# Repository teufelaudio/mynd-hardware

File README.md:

# Teufel MYND Hardware Repository
This repository contains all hardware related files including 3d models, schematics and pcb-layout files in various formats.

# Project structure
## `CAD/`
Contains 3d construction files in Rhino, STEP and STL formats. 
For every format, individual parts are available as direct download or a 'complete' package is avialable containing the entire model.
Due to size, the complete model in STL format is compressed into 'complete.zip'.

## `PCB_Schematics/`
### `./Altium`
Contains Altium Designer PCB and schematic files for all PCBs.
### `./KiCad`
Contains KiCad PCB and schematic files for all PCBs. Please note: These files were converted from the Altium working files for convenience and may still contain some  conversion errors.
### `./PDF`
Contains all schematic and assembly drawings exported to PDF from Altium files.

## Don't Yet Own a MYND Speaker!?
Purchase one [here](https://teufel.de/mynd)!

# Clone
```shell
git clone git@github.com:teufelaudio/mynd-hardware.git
```

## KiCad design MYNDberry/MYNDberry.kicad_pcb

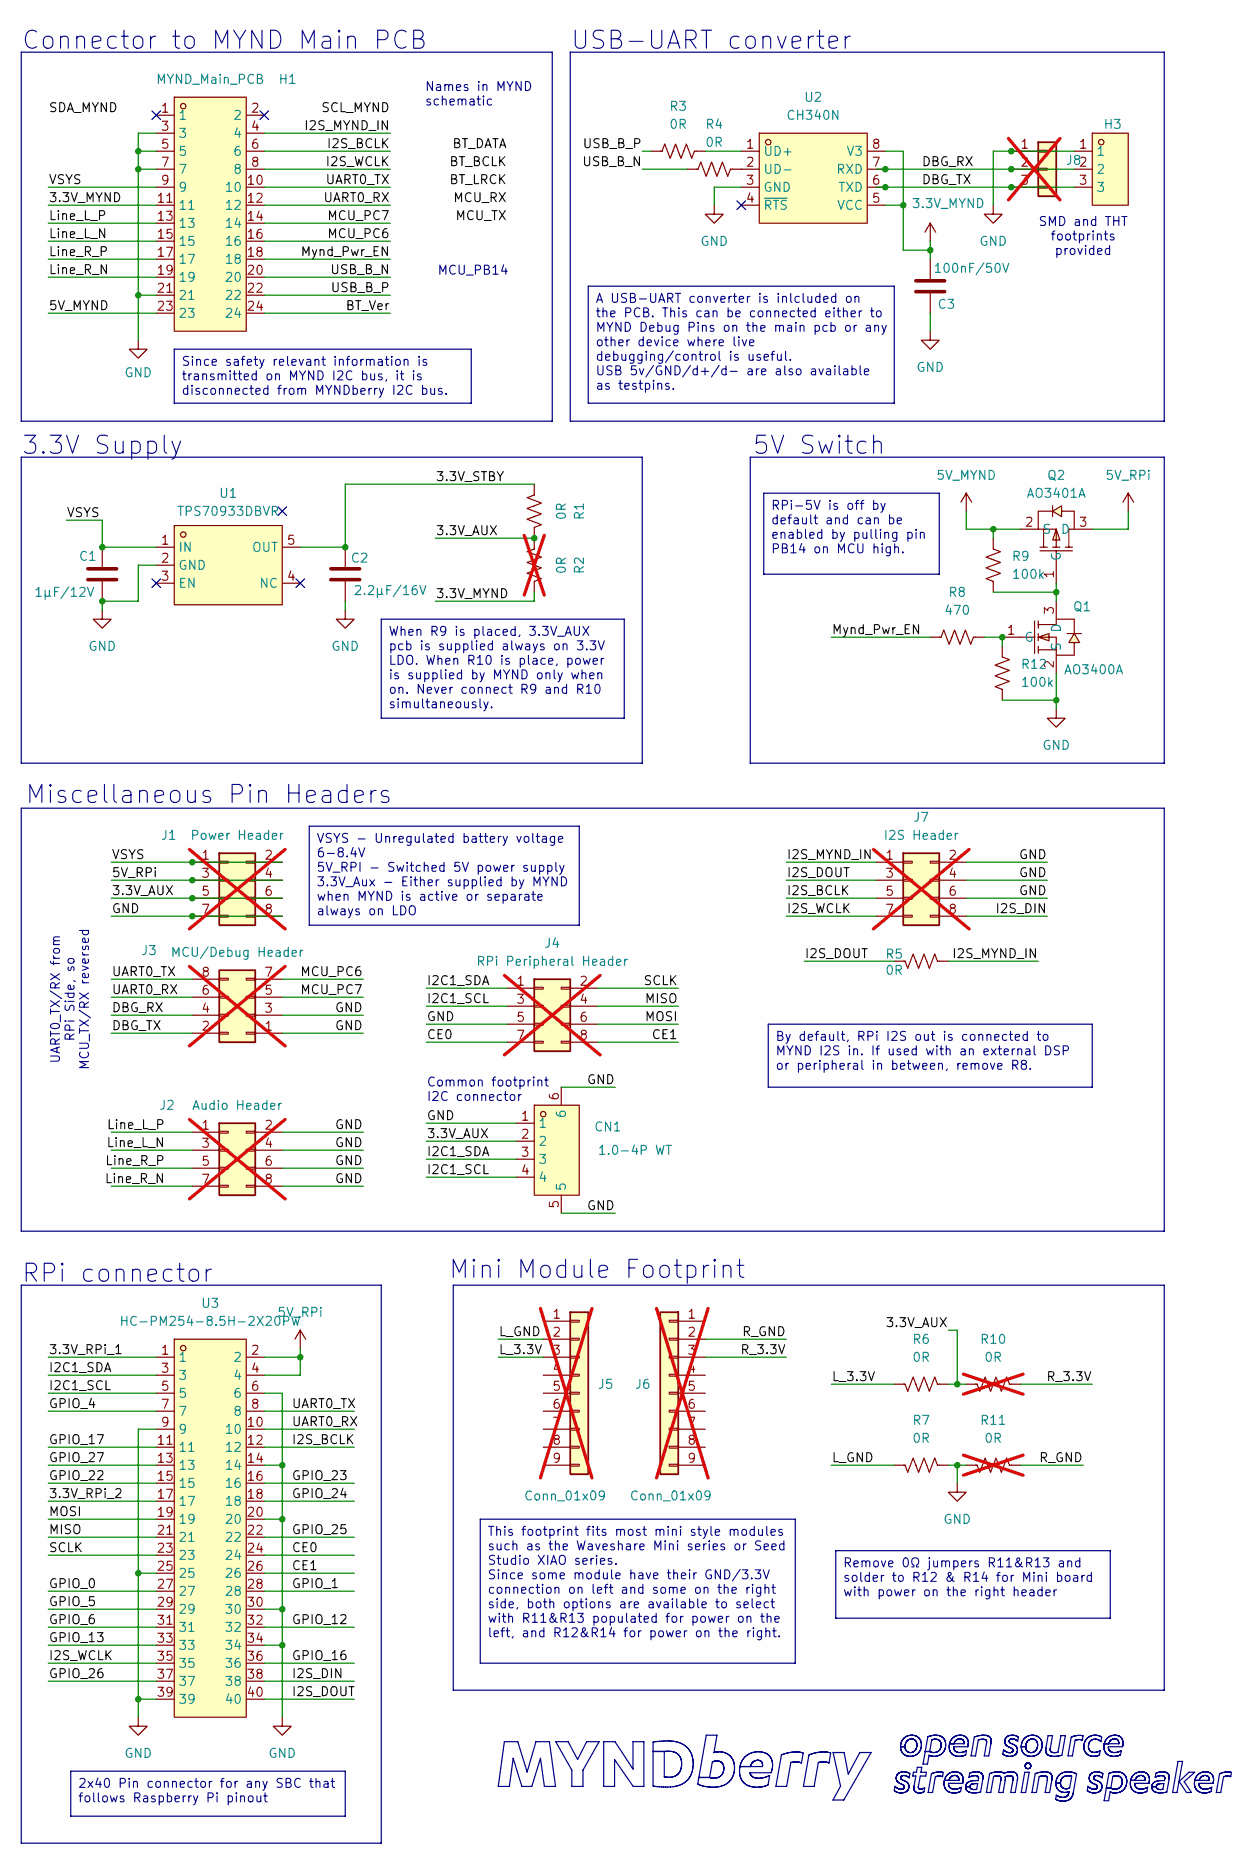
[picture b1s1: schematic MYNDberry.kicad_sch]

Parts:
C1: 1µF/12V; C_0603_1608Metric; LCSC C15008
C2: 2.2µF/16V; C_0603_1608Metric; LCSC C15008
C3: 100nF/50V; C_0603_1608Metric; LCSC C15008
CN1: 1.0-4P WT; CONN-SMD_4P-P1.00_SHOU-HAN_1.0-4P-WT; LCSC Part C2906270
H1: MYND_Main_PCB; HDR-SMD_24P-P2.54-V-F-R2-C12-S7.4; LCSC Part C3294470
H3: HX_PZ2.54-1X3P_WT; HDR-SMD_3P-P2.54-H-M_KH-2.54PH-1X3P-L13.5-WT; LCSC Part C46061676
J1: Power Header; PinHeader_2x04_P2.54mm_Small_Outline; not fitted
J2: Audio Header; PinHeader_2x04_P2.54mm_Small_Outline; not fitted
J3: MCU/Debug Header; PinHeader_2x04_P2.54mm_Small_Outline; not fitted
J4: RPi Peripheral Header; PinHeader_2x04_P2.54mm_Small_Outline; not fitted
J5: Conn_01x09; 9P_SolderPad_TH_Left; not fitted
J6: Conn_01x09; 9P_SolderPad_TH_Right; not fitted
J7: I2S Header; PinHeader_2x04_P2.54mm_Small_Outline; not fitted
J8: Conn_01x03; PinHeader_1x03_P2.54mm_Vertical; not fitted
Q1: AO3400A; SOT-23-3_L2.9-W1.3-P1.90-LS2.4-BR; LCSC Part C20917
Q2: AO3401A; SOT-23_L2.9-W1.3-P1.90-LS2.4-BR; LCSC Part C15127
R1, R3, R4, R5, R6, R7: 0R; R_0603_1608Metric; LCSC Part C21189
R2, R10, R11: 0R; R_0603_1608Metric; not fitted
R8: 470; R_0603_1608Metric; LCSC Part C23179
R9, R12: 100k; R_0603_1608Metric; LCSC Part C25803
U1: TPS70933DBVR; SOT-23-5_L3.0-W1.7-P0.95-LS2.8-BR; LCSC Part C89347
U2: CH340N; SOP-8_L4.9-W3.9-P1.27-LS6.0-BL; LCSC Part C2977777
U3: HC-PM254-8.5H-2X20PW; HDR-TH_40P-P2.54-H-F-R2-C20-S2.54-N; LCSC Part C22373943

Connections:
3.3V_MYND: C3.2, H1.11, R2.2, U2.5 (VCC), U2.8 (V3)
5V_MYND: H1.23, Q2.2 (S), R9.2
5V_RPi: J1.3, J1.4, Q2.3 (D), U3.2, U3.4
/3.3V_AUX: CN1.2, J1.5, J1.6, R1.2, R2.1, R6.2, R10.1
/3.3V_RPi_1: U3.1
/3.3V_RPi_2: U3.17
/3.3V_STBY: C2.2, R1.1, U1.5 (OUT)
/BT_Ver: H1.24
/CE0: J4.7, U3.24
/CE1: J4.8, U3.26
/DBG_RX: H3.2, J3.4, J8.2, U2.7 (RXD)
/DBG_TX: H3.3, J3.2, J8.3, U2.6 (TXD)
/GPIO_0: U3.27
/GPIO_1: U3.28
/GPIO_4: U3.7
/GPIO_5: U3.29
/GPIO_6: U3.31
/GPIO_12: U3.32
/GPIO_13: U3.33
/GPIO_16: U3.36
/GPIO_17: U3.11
/GPIO_22: U3.15
/GPIO_23: U3.16
/GPIO_24: U3.18
/GPIO_25: U3.22
/GPIO_26: U3.37
/GPIO_27: U3.13
/I2C1_SCL: CN1.4, J4.3, U3.5
/I2C1_SDA: CN1.3, J4.1, U3.3
/I2S_BCLK: H1.6, J7.5, U3.12
/I2S_DIN: J7.8, U3.38
/I2S_DOUT: J7.3, R5.1, U3.40
/I2S_MYND_IN: H1.4, J7.1, R5.2
/I2S_WCLK: H1.8, J7.7, U3.35
/L_3.3V: J5.3, R6.1
/L_GND: J5.2, R7.1
/Line_L_N: H1.15, J2.3
/Line_L_P: H1.13, J2.1
/Line_R_N: H1.19, J2.7
/Line_R_P: H1.17, J2.5
/MCU_PC6: H1.16, J3.7
/MCU_PC7: H1.14, J3.5
/MISO: J4.4, U3.21
/MOSI: J4.6, U3.19
/Mynd_Pwr_EN: H1.18, R8.2
/R_3.3V: J6.3, R10.2
/R_GND: J6.2, R11.2
/SCLK: J4.2, U3.23
/UART0_RX: H1.12, J3.6, U3.10
/UART0_TX: H1.10, J3.8, U3.8
/USB_B_N: H1.20, R4.2
/USB_B_P: H1.22, R3.2
/VSYS: C1.2, H1.9, J1.1, J1.2, U1.1 (IN)
GND: C1.1, C2.1, C3.1, CN1.1, CN1.5, CN1.6, H1.3, H1.5, H1.7, H1.21, H3.1, J1.7, J1.8, J2.2, J2.4, J2.6, J2.8, J3.1, J3.3, J4.5, J7.2, J7.4, J7.6, J8.1, Q1.2 (S), R7.2, R11.1, R12.1, U1.2 (GND), U2.3 (GND), U3.6, U3.9, U3.14, U3.20, U3.25, U3.30, U3.34, U3.39
unnamed: Q1.3 (D), Q2.1 (G), R9.1
unnamed: Q1.1 (G), R8.1, R12.2
unnamed: R3.1, U2.1 (UD+)
unnamed: R4.1, U2.2 (UD-)

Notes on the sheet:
RPi connector
SMD and THT footprints provided
Miscellaneous Pin Headers
3.3V Supply
Mini Module Footprint
USB-UART converter
Connector to MYND Main PCB
MCU_PB14
5V Switch
UART0_TX/RX from RPi Side, so MCU_TX/RX reversed
Common footprint I2C connector
Names in MYND schematic
When R9 is placed, 3.3V_AUX pcb is supplied always on 3.3V LDO. When R10 is place, power is supplied by MYND only when on. Never connect R9 and R10 simultaneously.
This footprint fits most mini style modules such as the Waveshare Mini series or Seed Studio XIAO series. Since some module have their GND/3.3V connection on left and some on the right side, both options are available to select with R11&R13 populated for power on the left, and R12&R14 for power on 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
Since safety relevant information is transmitted on MYND I2C bus, it is disconnected from MYNDberry I2C bus.
Remove 0Ω jumpers R11&R13 and solder to R12 & R14 for Mini board with power on the right header
By default, RPi I2S out is connected to MYND I2S in. If used with an external DSP or peripheral in between, remove R8.
VSYS - Unregulated battery voltage 6-8.4V 5V_RPI - Switched 5V power supply 3.3V_Aux - Either supplied by MYND when MYND is active or separate always on LDO
A USB-UART converter is inlcluded on the PCB. This can be connected either to MYND Debug Pins on the main pcb or any other device where live debugging/control is useful. USB 5v/GND/d+/d- are also available as testpins.
RPi-5V is off by default and can be enabled by pulling pin PB14 on MCU high.
2x40 Pin connector for any SBC that follows Raspberry Pi pinout

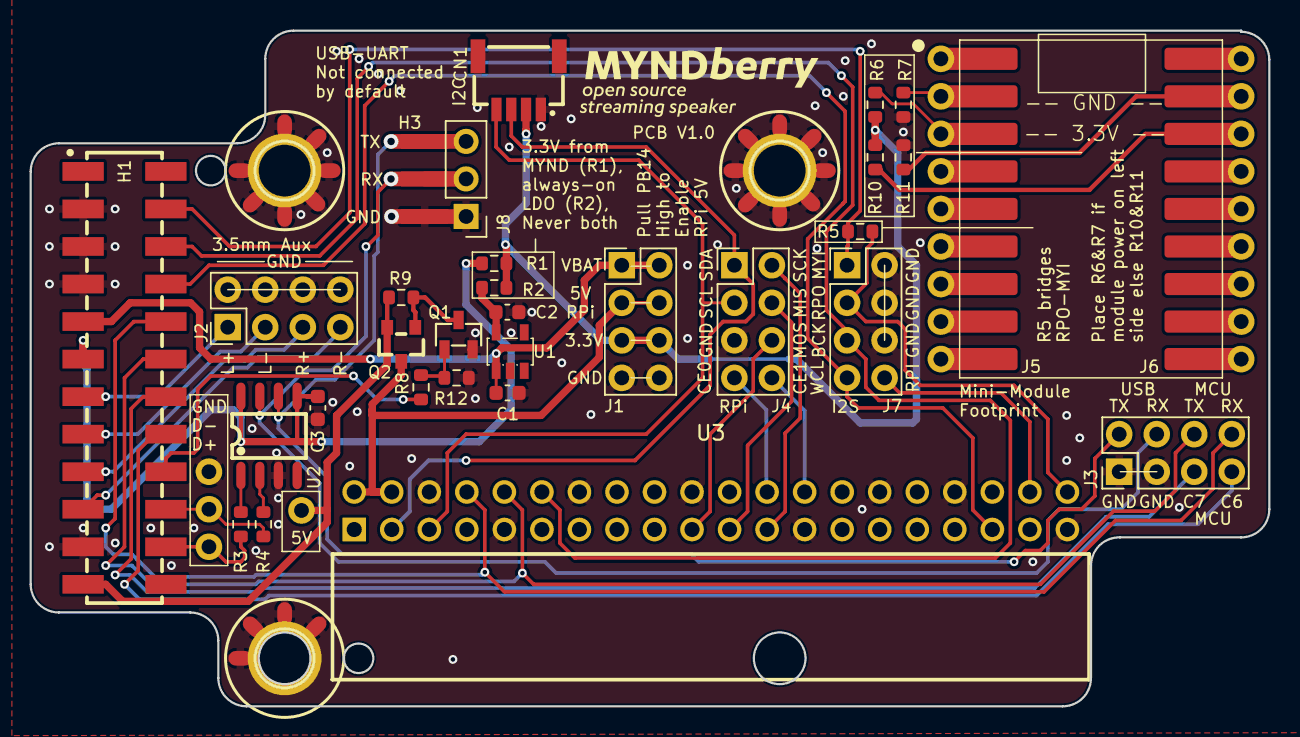
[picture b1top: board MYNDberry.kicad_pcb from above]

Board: 2 copper layers, 83.8 x 45.7 mm, 31 parts (0 on the bottom side), 40 nets.

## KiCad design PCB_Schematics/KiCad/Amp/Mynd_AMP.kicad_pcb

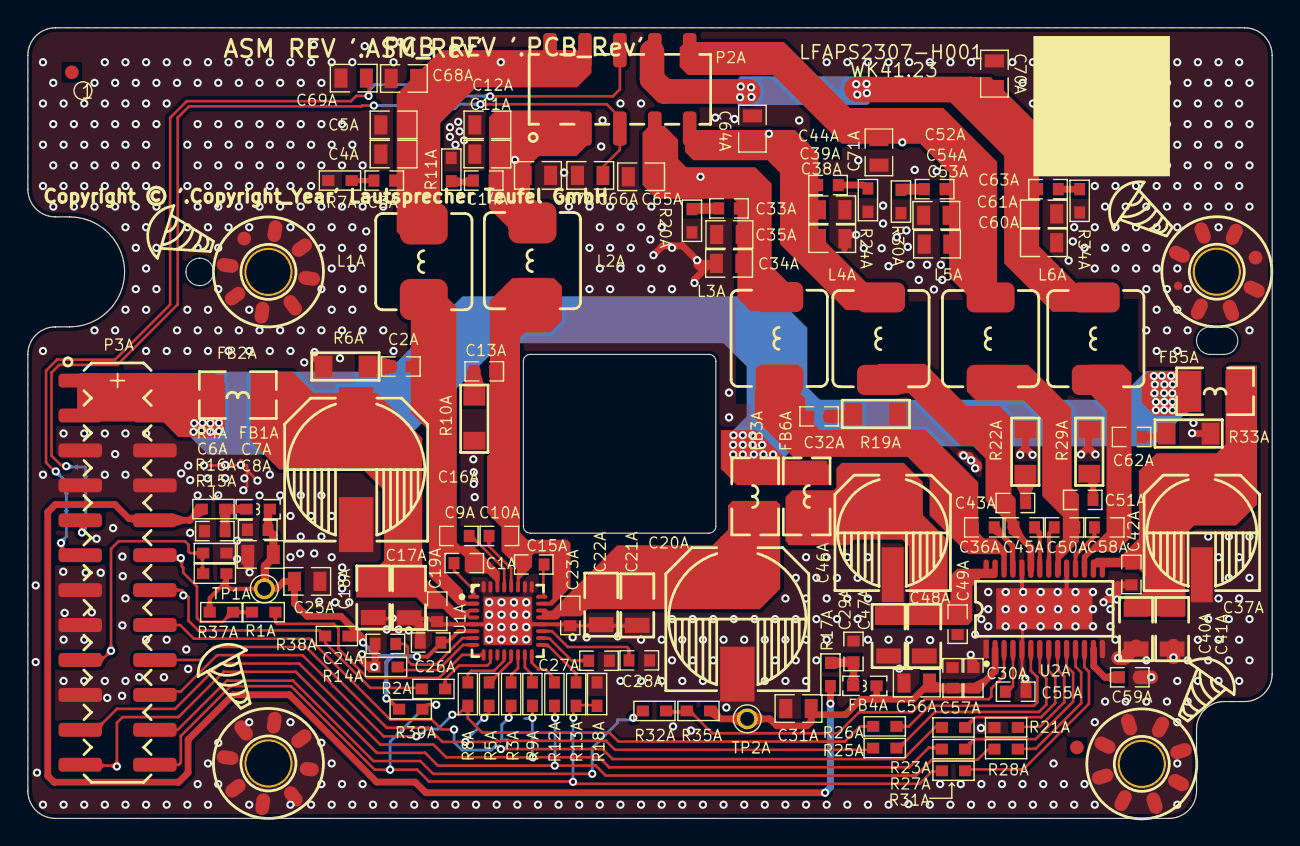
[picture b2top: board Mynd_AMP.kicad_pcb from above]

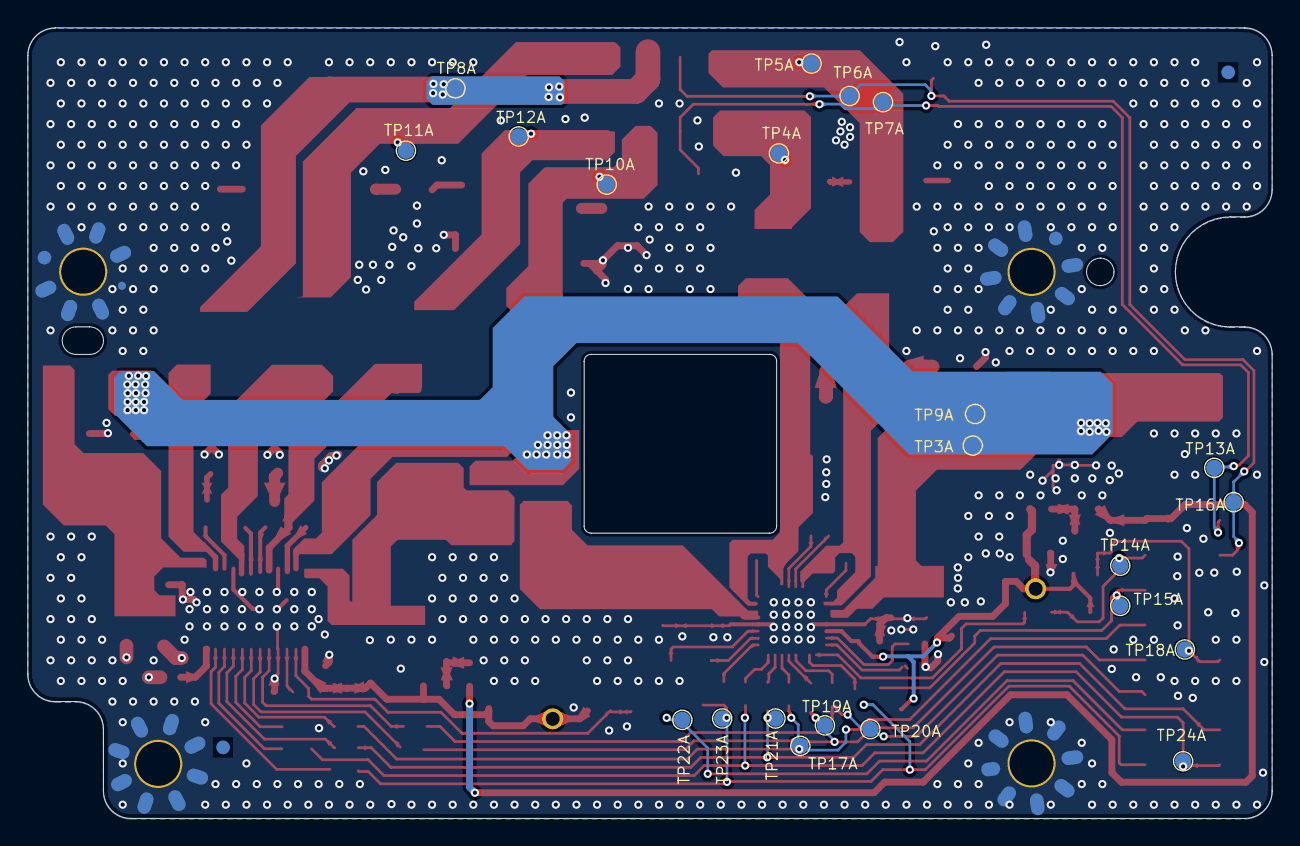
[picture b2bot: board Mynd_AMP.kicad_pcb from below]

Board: 2 copper layers, 90.5 x 57.5 mm, 159 parts (22 on the bottom side), 77 nets.

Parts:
C1A, C9A, C10A, C15A: 470nF; C0603X100
C2A, C13A, C32A, C43A, C51A, C62A: 330pF; C0603X80
C3A, C14A, C33A, C44A, C52A, C63A: 10nF; C0603X100
C4A, C11A: 680nF; C0805_125
C5A, C12A, C35A, C39A, C54A, C61A, C64A, C65A, C66A, C67A, C68A, C69A, C70A, C71A: 1nF; C0805_125
C6A, C7A, C19A, C23A, C26A, C29A, C30A, C42A, C49A, C57A: 100nF; C0603X105
C8A, C31A: 22uF; C0805_145
C16A, C20A: 470uF; ECAP_SMD_1000X1000
C17A, C18A, C21A, C22A, C40A, C41A, C47A, C48A: 10uF; C1206
C24A, C27A, C28A, C55A, C59A: 1uF; C0603X105
C25A, C56A: 4.7uF; C0805_145
C34A, C38A, C53A, C60A: 330nF; C0805_125
C36A, C45A, C50A, C58A: 220nF; C0603X100
C37A, C46A: 220uF; ECAP_SMD_800X1000
FB1A, FB4A: 600R; L0603
FB2A, FB3A, FB5A, FB6A: 56R; L1612
L1A, L2A: 4.7uH; IND_SMD_YT_SQU_L78XW70XH50
L3A, L4A, L5A, L6A: 10uH; IND_SMD_YT_SQU_L78XW70XH30
MH1A, MH2A, MH3A, MH4A: SCREW_HOLE_D32; SCREW_D32
MK_T1A, MK_T2A: MARK
P2A: 2 x 5P 2.54mm; female_2X5_254
P3A: 2 x 12P 2.54mm; Pin_Header_SMD_2X12_254
R1A, R2A, R13A, R31A, R32A: 10R; R0603
R3A, R5A, R8A, R9A, R12A, R14A, R23A, R25A, R26A, R27A, R28A: 0R; R0603
R4A, R17A: 2.2R; R0603
R6A, R10A, R19A, R22A, R29A, R33A: 10R; R1206
R7A, R11A, R20A, R24A, R30A, R34A: 3.3R; R0603
R15A: 100k; R0603
R16A, R18A, R21A, R37A, R38A: 10k; R0603
R35A: 4.7k; R0603
R39A: NC; R0603
TP1A, TP2A: TP_T_60_40
TP3A, TP4A, TP5A, TP6A, TP7A, TP8A, TP9A, TP10A, TP11A, TP12A, TP13A, TP14A, TP15A, TP16A, TP17A, TP18A, TP19A, TP20A, TP21A, TP22A, TP23A, TP24A: TP12; TP120
Teufel_ASM_Label1A: =Comment/Name; Teufel_ASM_Rev
Teufel_Copyright1A: =Comment/Name; TEUFEL_COPYRIGHT
Teufel_PCB_Label1A: =Comment/Name; Teufel_PCB_Rev
Teufel_PCB_Logo1A: T.3.0.0040-2.1; Teufel_NoLogo
U1A: TAS5825PRHBR; QFN32_500X500X100_50_P350X350
U2A: TAS5805MPWPR; TSSOP28(PWP)

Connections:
3V3_STB: P3A.10, R4A.2, R17A.2
3V3_SW: C7A.1, C8A.1, C25A.1, C26A.1, FB1A.2, R15A.1, R37A.1, R38A.1, R39A.1, TP1A.1, U1A.6
3V3_TW: C30A.1, C31A.1, C56A.1, C57A.1, FB4A.2, R35A.1, TP2A.1, U2A.2
24V: FB2A.1, FB3A.1, FB5A.1, FB6A.2, P3A.1, P3A.2, P3A.3, P3A.4, TP3A.1, TP9A.1
Amp_Ver: P3A.17, R15A.2, R16A.1, TP18A.1
BatVCC: C66A.1, P2A.5, P3A.9, TP7A.1, TP13A.1
C_Open: C69A.1, P2A.6, P3A.11, TP6A.1, TP16A.1
Env_Track: P3A.14, R2A.2, R38A.2, TP15A.1
GND: C4A.2, C5A.2, C6A.2, C7A.2, C8A.2, C11A.2, C12A.2, C16A.2, C17A.2, C18A.2, C19A.2, C20A.2, C21A.2, C22A.2, C23A.2, C24A.1, C25A.2, C26A.2, C27A.1, C28A.1, C29A.2, C30A.2, C31A.2, C34A.2, C35A.2, C37A.2, C38A.2, C39A.2, C40A.2, C41A.2, C42A.2, C46A.2, C47A.2, C48A.2, C49A.2, C53A.2, C54A.2, C55A.1, C56A.2, C57A.2, C59A.1, C60A.2, C61A.2, C64A.2, C65A.2, C66A.2, C67A.2, C68A.2, C69A.2, C70A.2, C71A.2, MH1A.1, MH2A.1, MH3A.1, MH4A.1, P3A.5, P3A.6, P3A.7, P3A.8, P3A.13, P3A.15, P3A.19, R6A.2, R7A.2, R10A.1, R11A.2, R14A.1, R16A.2, R18A.2, R19A.2, R20A.2, R21A.2, R22A.1, R24A.2, R29A.2, R30A.2, R33A.1, R34A.2, U1A.0, U1A.5, U1A.20, U1A.25, U1A.26, U1A.31, U1A.32, U2A.0, U2A.1, U2A.5, U2A.14, U2A.19, U2A.24
I2S_BCLK: P3A.18, R5A.1, R25A.1, TP19A.1
I2S_DATA: P3A.16, R3A.1, R23A.1, TP17A.1
I2S_LRCK: P3A.20, R8A.1, R26A.1, TP20A.1
NetC1A_1: C1A.1, C2A.2, C9A.2, L1A.1, U1A.2, U1A.30
NetC1A_2: C1A.2, U1A.1
NetC2A_1: C2A.1, R6A.1
NetC3A_2: C3A.2, R7A.1
NetC6A_1: C6A.1, FB1A.1, R4A.1
NetC9A_1: C9A.1, U1A.29
NetC10A_1: C10A.1, C13A.1, C15A.2, L2A.1, U1A.23, U1A.27
NetC10A_2: C10A.2, U1A.28
NetC13A_2: C13A.2, R10A.2
NetC14A_1: C14A.1, R11A.1
NetC15A_1: C15A.1, U1A.24
NetC16A_1: C16A.1, C17A.1, C18A.1, C19A.1, FB2A.2, U1A.3, U1A.4
NetC20A_1: C20A.1, C21A.1, C22A.1, C23A.1, FB3A.2, U1A.21, U1A.22
NetC24A_2: C24A.2, U1A.7
NetC27A_2: C27A.2, U1A.18
NetC28A_2: C28A.2, U1A.19
NetC29A_1: C29A.1, FB4A.1, R17A.1
NetC32A_1: C32A.1, R19A.1
NetC32A_2: C32A.2, C36A.1, L3A.1, U2A.26
NetC33A_2: C33A.2, R20A.1
NetC36A_2: C36A.2, U2A.25
NetC37A_1: C37A.1, C40A.1, C41A.1, C42A.1, FB5A.2, U2A.15, U2A.16
NetC43A_1: C43A.1, C45A.2, L4A.1, U2A.23
NetC43A_2: C43A.2, R22A.2
NetC44A_1: C44A.1, R24A.1
NetC45A_1: C45A.1, U2A.22
NetC46A_1: C46A.1, C47A.1, C48A.1, C49A.1, FB6A.1, U2A.27, U2A.28
NetC50A_1: C50A.1, C51A.2, L5A.1, U2A.20
NetC50A_2: C50A.2, U2A.21
NetC51A_1: C51A.1, R29A.1
NetC52A_2: C52A.2, R30A.1
NetC55A_2: C55A.2, U2A.4
NetC58A_1: C58A.1, U2A.18
NetC58A_2: C58A.2, C62A.1, L6A.1, U2A.17
NetC59A_2: C59A.2, U2A.13
NetC62A_2: C62A.2, R33A.2
NetC63A_1: C63A.1, R34A.1
NetR1A_1: R1A.1, U1A.9
NetR2A_1: R2A.1, U1A.10
NetR3A_2: R3A.2, U1A.14
NetR5A_2: R5A.2, U1A.13
NetR8A_2: R8A.2, U1A.12
NetR9A_2: R9A.2, U1A.15
NetR12A_2: R12A.2, U1A.16
NetR13A_1: R13A.1, U1A.17
NetR14A_2: R14A.2, U1A.8
NetR21A_1: R21A.1, U2A.9
NetR23A_2: R23A.2, U2A.8
NetR25A_2: R25A.2, U2A.7
NetR26A_2: R26A.2, U2A.6
NetR27A_2: R27A.2, U2A.10
NetR28A_2: R28A.2, U2A.11
NetR31A_1: R31A.1, U2A.12
NetR32A_1: R32A.1, R35A.2, U2A.3
SCL: P3A.23, R12A.1, R28A.1, TP24A.1
SDA: P3A.21, R9A.1, R27A.1, TP21A.1
SW_N: C11A.1, C12A.1, C14A.2, C67A.1, L2A.2, P2A.1, P2A.3, TP4A.1
SW_P: C3A.1, C4A.1, C5A.1, C68A.1, L1A.2, P2A.2, P2A.4, TP5A.1
TW_L_N: C52A.1, C53A.1, C54A.1, C71A.1, L5A.2, P2A.10, TP11A.1
TW_L_P: C60A.1, C61A.1, C63A.2, C70A.1, L6A.2, P2A.8, TP8A.1
TW_R_N: C38A.1, C39A.1, C44A.2, C64A.1, L4A.2, P2A.9, TP12A.1
TW_R_P: C33A.1, C34A.1, C35A.1, C65A.1, L3A.2, P2A.7, TP10A.1
~Amp_PDN: P3A.24, R13A.2, R18A.1, R31A.2, R39A.2, TP23A.1
~Amp_SwFlt: P3A.12, R1A.2, R37A.2, TP14A.1
~Amp_TwFlt: P3A.22, R32A.2, TP22A.1

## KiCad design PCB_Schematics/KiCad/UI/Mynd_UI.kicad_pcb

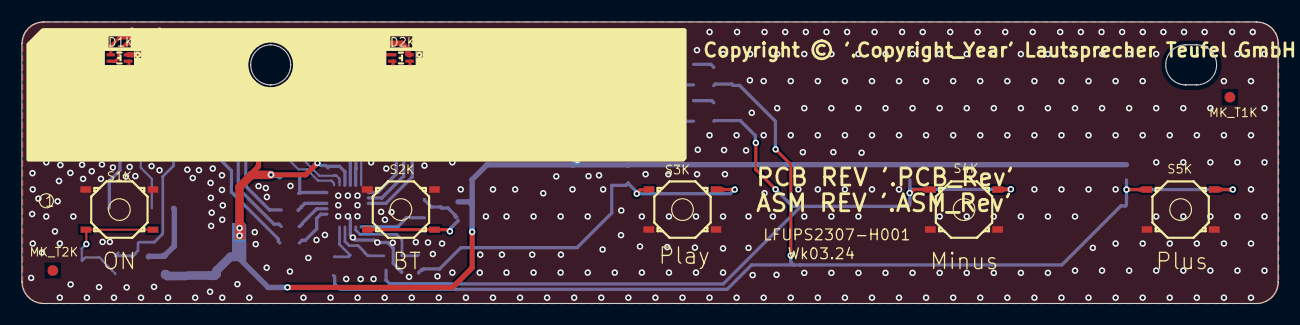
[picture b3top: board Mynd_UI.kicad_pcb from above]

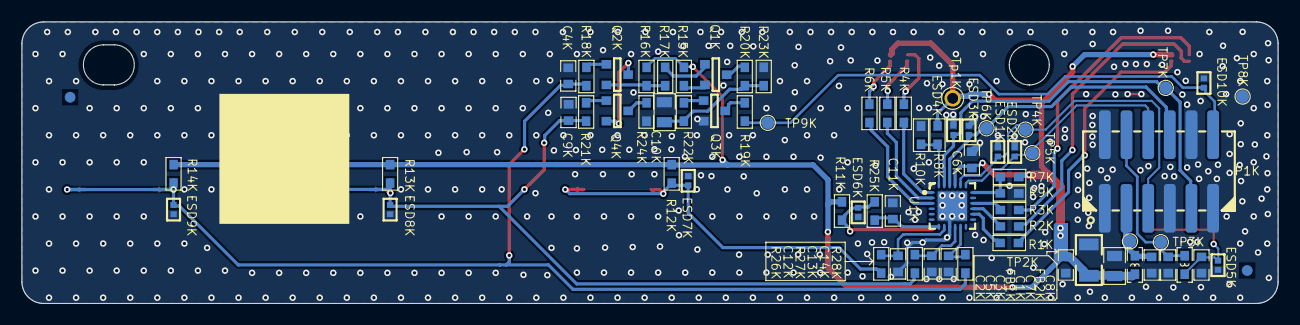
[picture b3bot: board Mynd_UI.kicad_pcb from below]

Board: 2 copper layers, 116.0 x 26.0 mm, 82 parts (69 on the bottom side), 43 nets.

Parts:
C1K, C2K, C4K, C6K, C9K: 100nF; C0603X100
C3K, C10K: 10uF; C0805_145
C5K: 22uF; C1206
C7K, C8K: 33pF; C0603X80
C11K, C12K, C13K, C14K: NC; C0603X100
D1K, D2K: JH-CRGBB06GTP014; LED_SMD_F_T_160X80X60
ESD1K, ESD2K, ESD3K, ESD4K, ESD6K, ESD7K, ESD8K, ESD9K, ESD10K: CESD0501CU; DFN2_100X60X50_65
ESD5K: BDFN2C121V; DFN2_100X60X50_65
FB1K, FB2K: 600R; L0603
MK_T1K, MK_T2K: MARK
P1K: WB200AL-12; WB200AL_2x6P
Q1K, Q2K, Q4K: CJ3401; SOT23-GSD
Q3K: 2N7002K; SOT23-GSD
R1K, R2K, R5K, R6K: 22R; R0603
R3K, R4K: 75R; R0603
R7K, R8K: 100R; R0603
R9K, R10K, R16K, R22K: 10k; R0603
R11K, R12K, R13K, R14K: 100k; R0603
R15K, R24K: 0R; R0603
R17K: 4.7k; R0603
R18K, R21K: 150k; R0603
R19K: 10R; R0603
R20K: 680k; R0603
R23K: 1M; R0603
R25K, R26K, R27K, R28K: 1k; R0603
S1K, S2K, S3K, S4K, S5K: TC-1316A-H1.5-180GF; TACT_SW_SMD_52X52X15
TP2K, TP3K, TP4K, TP5K, TP6K, TP7K, TP8K, TP9K: TP12; TP120
Teufel_ASM_Label1K: =Comment/Name; Teufel_ASM_Rev
Teufel_Copyright1K: =Comment/Name; TEUFEL_COPYRIGHT
Teufel_PCB_Label1K: =Comment/Name; Teufel_PCB_Rev
Teufel_PCB_Logo1K: T.3.0.0040-3.2; Teufel_NoLogo
Tp1K: TP_T_60_40
U1K: AW9523BTQR; QFN24_400X400X100_50_P270X270

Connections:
3V3_LED: C2K.1, C3K.1, C5K.2, C6K.2, D1K.C, D2K.C, FB1K.1, R7K.2, R8K.2, R11K.1, R12K.1, R13K.1, R14K.1, R15K.1, R16K.2, Tp1K.1, U1K.21
3V3_STB: C1K.1, FB1K.2, P1K.3, TP2K.1
Btn_BT: ESD6K.2, R11K.2, R25K.2, S2K.3, S2K.4
Btn_Minus: C9K.1, ESD8K.2, R13K.2, R21K.1, R27K.2, S4K.3, S4K.4
Btn_On: C8K.1, ESD5K.2, FB2K.2, S1K.3, S1K.4
Btn_Play: ESD7K.2, R12K.2, R26K.2, S3K.3, S3K.4
Btn_Plus: C4K.1, ESD9K.2, R14K.2, R18K.1, R28K.2, S5K.3, S5K.4
GND: C1K.2, C2K.2, C3K.2, C4K.2, C5K.1, C6K.1, C7K.2, C8K.2, C9K.2, C10K.2, C11K.2, C12K.2, C13K.2, C14K.2, ESD1K.1, ESD2K.1, ESD3K.1, ESD4K.1, ESD5K.1, ESD6K.1, ESD7K.1, ESD8K.1, ESD9K.1, ESD10K.1, P1K.1, P1K.2, P1K.7, P1K.10, P1K.11, Q3K.S, R9K.2, R10K.2, R23K.1, R24K.1, S1K.1, S1K.2, S2K.1, S2K.2, S3K.1, S3K.2, S4K.1, S4K.2, S5K.1, S5K.2, TP8K.1, U1K.0, U1K.9
I2C2_SCL: ESD2K.2, P1K.6, TP5K.1, U1K.19
I2C2_SDA: ESD1K.2, P1K.5, TP4K.1, U1K.20
MCU_RST: ESD10K.2, P1K.12, R19K.1, TP9K.1
NetC10K_1: C10K.1, R20K.2, R22K.1, R23K.2
NetC11K_1: C11K.1, R25K.1, U1K.7
NetC12K_1: C12K.1, R26K.1, U1K.8
NetC13K_1: C13K.1, R27K.1, U1K.10
NetC14K_1: C14K.1, R28K.1, U1K.11
NetD1K_B: D1K.B, R1K.1
NetD1K_G: D1K.G, R2K.1
NetD1K_R: D1K.R, R3K.1
NetD2K_B: D2K.B, R6K.1
NetD2K_G: D2K.G, R5K.1
NetD2K_R: D2K.R, R4K.1
NetQ1K_D: Q1K.D, R20K.1
NetQ1K_G: Q1K.G, R17K.2
NetQ1K_S: Q1K.S, R15K.2
NetQ2K_D: Q2K.D, Q4K.S
NetQ2K_G: Q2K.G, R18K.2
NetQ2K_S: Q2K.S, R16K.1, R17K.1
NetQ3K_D: Q3K.D, R19K.2
NetQ3K_G: Q3K.G, R22K.2
NetQ4K_D: Q4K.D, R24K.2
NetQ4K_G: Q4K.G, R21K.2
NetR1K_2: R1K.2, U1K.14
NetR2K_2: R2K.2, U1K.15
NetR3K_2: R3K.2, U1K.16
NetR4K_2: R4K.2, U1K.1
NetR5K_2: R5K.2, U1K.2
NetR6K_2: R6K.2, U1K.3
NetR7K_1: R7K.1, R9K.1, U1K.18
NetR8K_1: R8K.1, R10K.1, U1K.24
\P_Btn: C7K.1, FB2K.1, P1K.4, TP3K.1
\UI_Int: ESD3K.2, P1K.8, TP6K.1, U1K.22
\UI_Rst: ESD4K.2, P1K.9, TP7K.1, U1K.23

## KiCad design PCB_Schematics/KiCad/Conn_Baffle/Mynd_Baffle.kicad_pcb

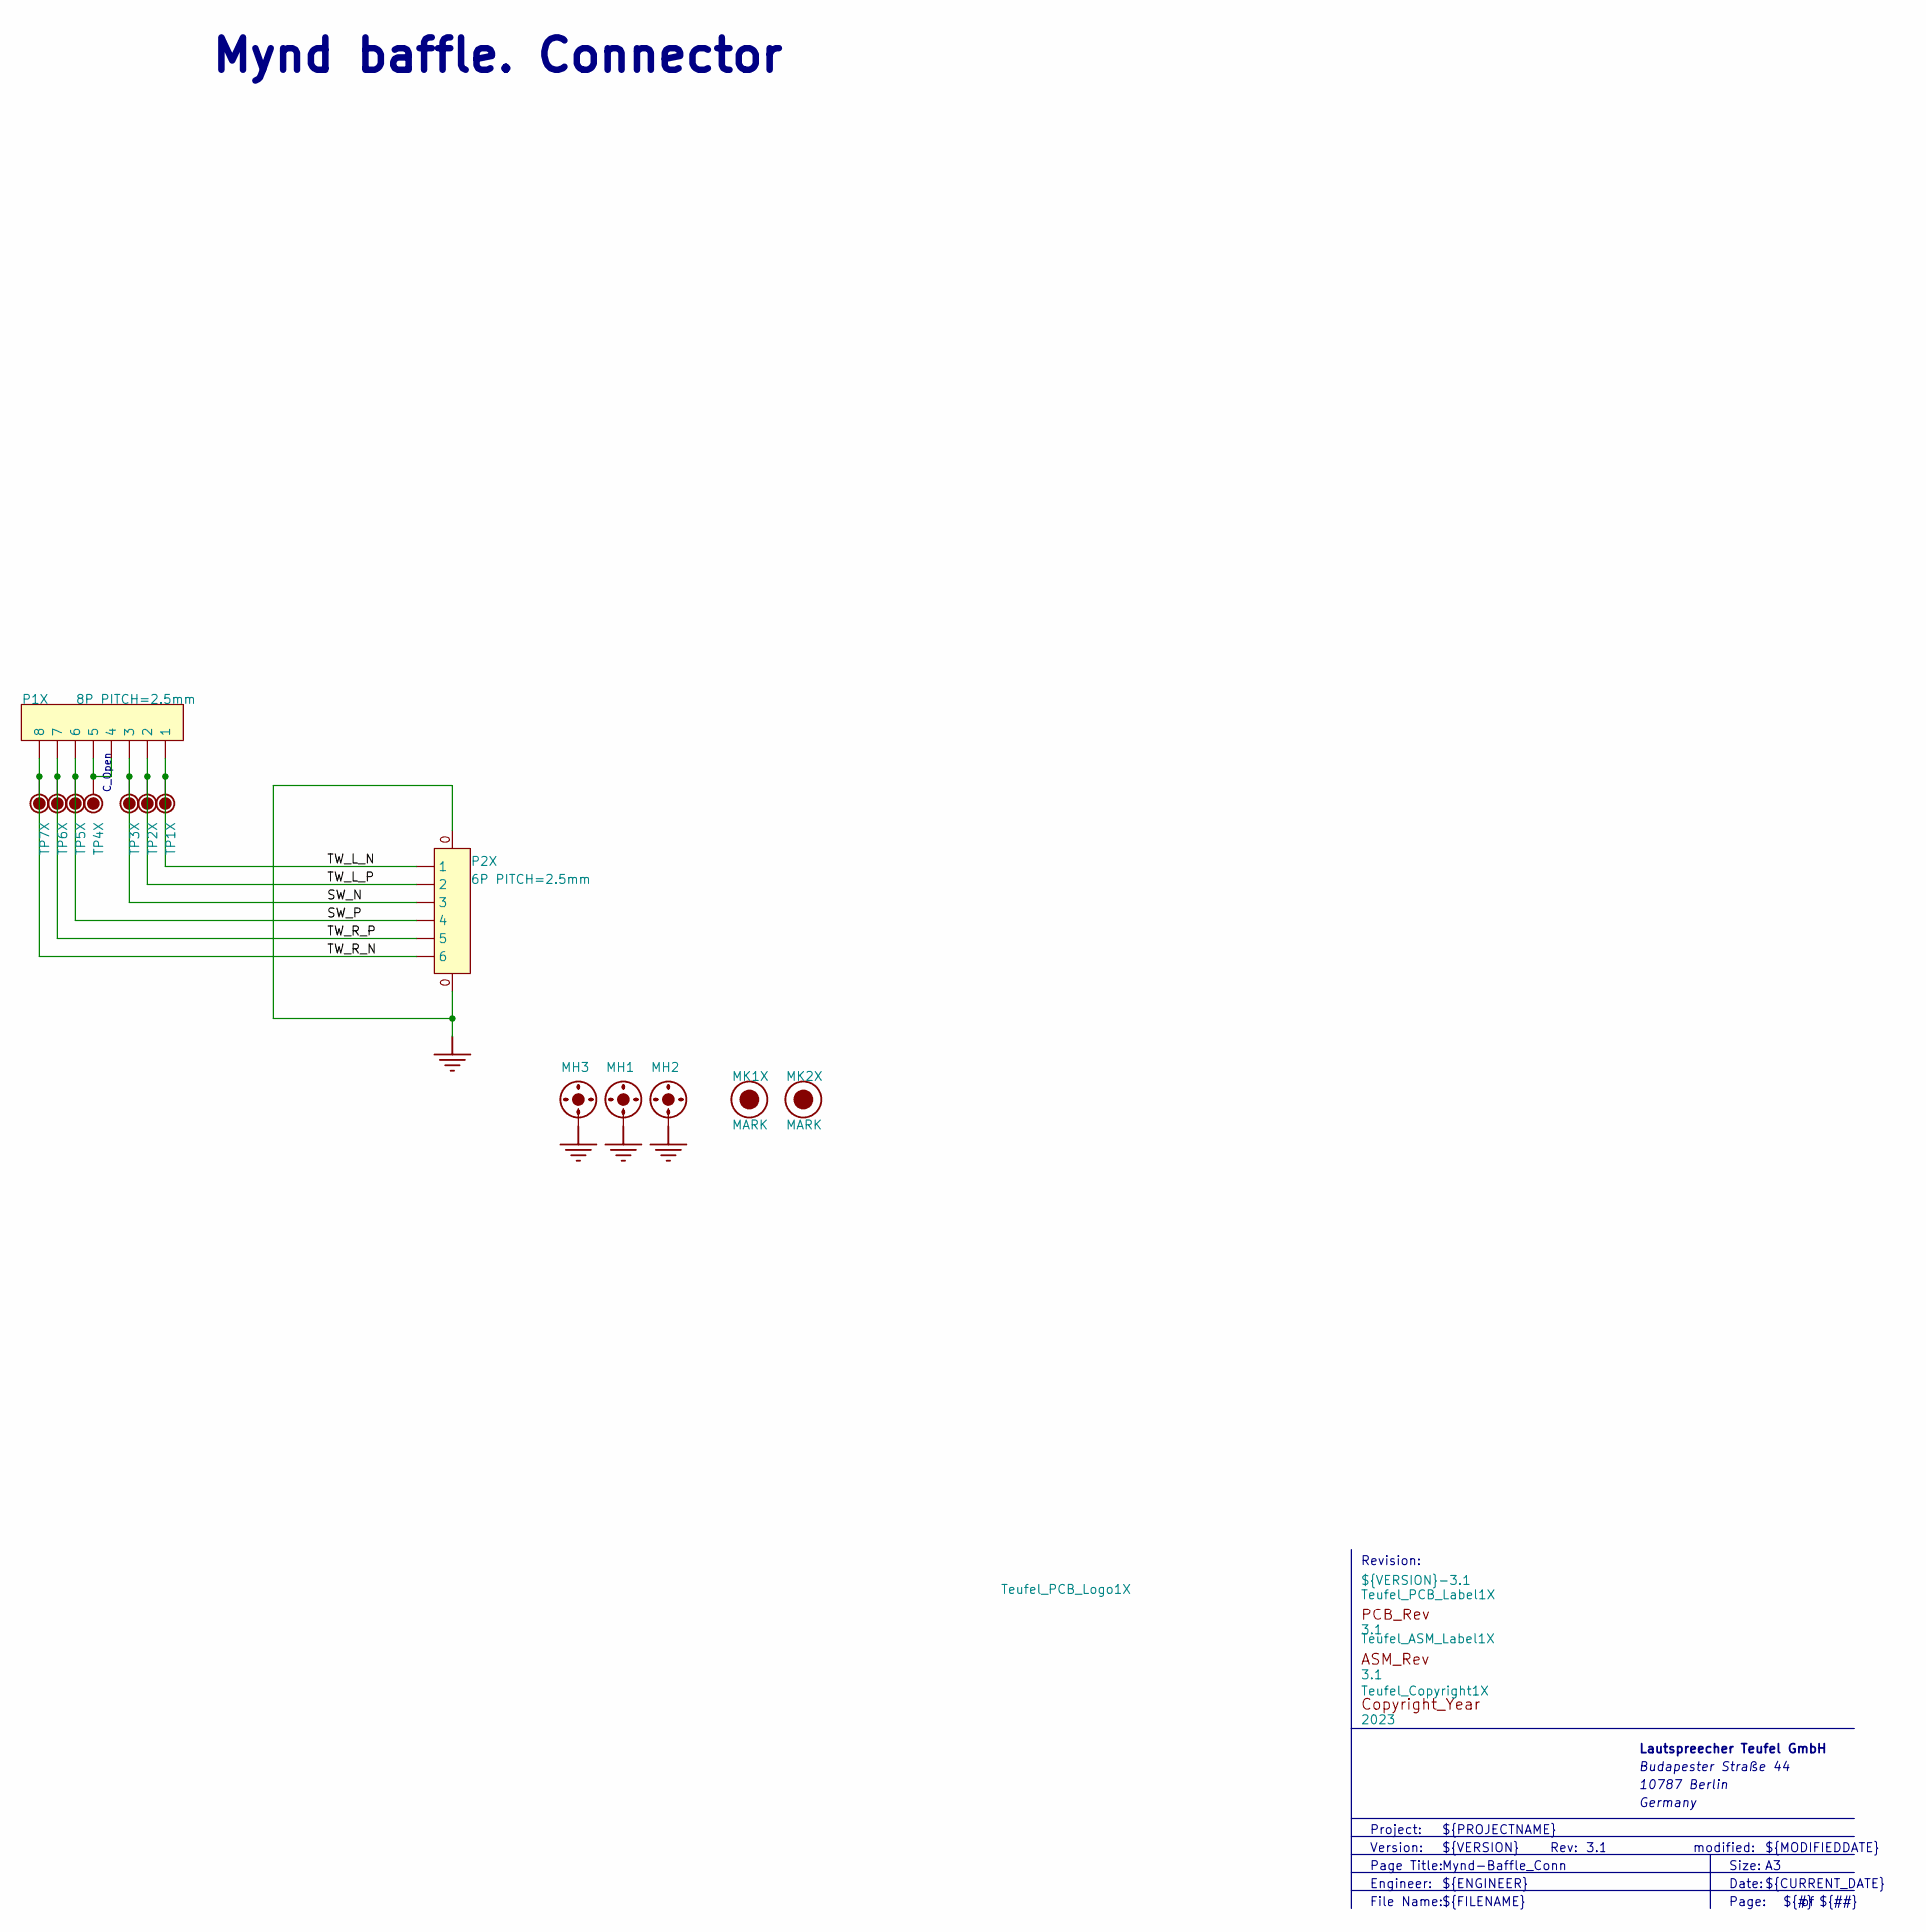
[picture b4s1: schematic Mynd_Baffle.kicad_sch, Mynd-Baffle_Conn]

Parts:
MH1, MH3: SCREW_HOLE_D35; SCREW_D35
MH2: HOLD_D35
MK1X, MK2X: MARK
P1X: 8P PITCH=2.5mm; TSB1_05282; PART_NUMBER 8P PITCH=2.5mm
P2X: 6P PITCH=2.5mm; CON_250_SMD_V_6P; PART_NUMBER 6P PITCH=2.5mm
TP1X, TP2X, TP3X, TP4X, TP5X, TP6X, TP7X: TP12; TP120
Teufel_ASM_Label1X: 3.1; Teufel_ASM_Rev
Teufel_Copyright1X: 2023; TEUFEL_COPYRIGHT
Teufel_PCB_Label1X: 3.1; Teufel_PCB_Rev
Teufel_PCB_Logo1X: ${VERSION}-${REVISION}; Teufel_NoLogo

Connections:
GND: MH1.1, MH2.1, MH3.1, P2X.0
NetP1X_4: P1X.4, P1X.5, TP4X.1
SW_N: P1X.3, P2X.3, TP3X.1
SW_P: P1X.6, P2X.4, TP5X.1
TW_L_N: P1X.1, P2X.1, TP1X.1
TW_L_P: P1X.2, P2X.2, TP2X.1
TW_R_N: P1X.8, P2X.6, TP7X.1
TW_R_P: P1X.7, P2X.5, TP6X.1

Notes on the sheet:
modified:
C_Open
${CURRENT_DATE}
Mynd baffle. Connector
Version:
Date:
File Name:
Page Title:
${FILENAME}
${MODIFIEDDATE}
Lautspreecher Teufel GmbH
Engineer:
${TITLE}
10787 Berlin
Budapester Straße 44
${##}
${ENGINEER}
Project:
Rev:
${PROJECTNAME}
${REVISION}
${VERSION}
Revision:
${#}
Size:
Page:
Germany

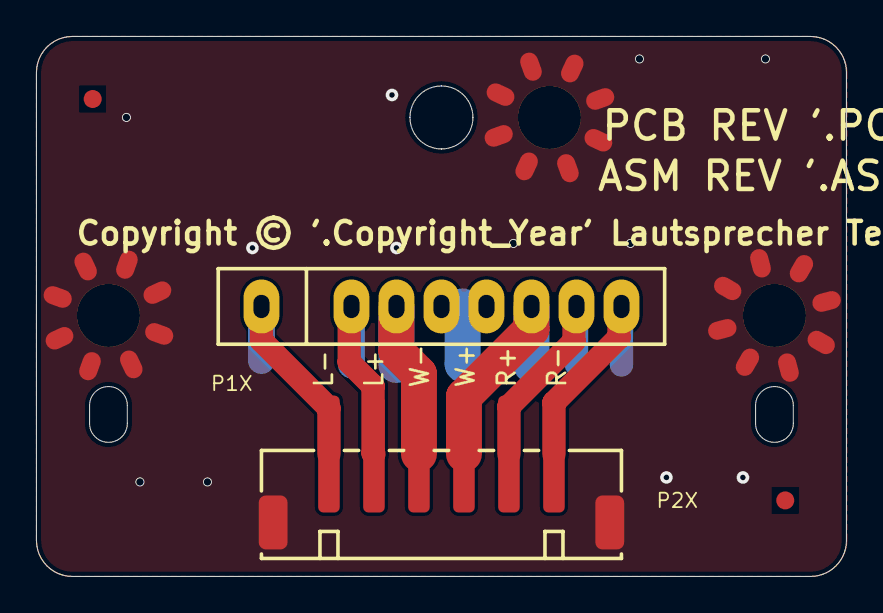
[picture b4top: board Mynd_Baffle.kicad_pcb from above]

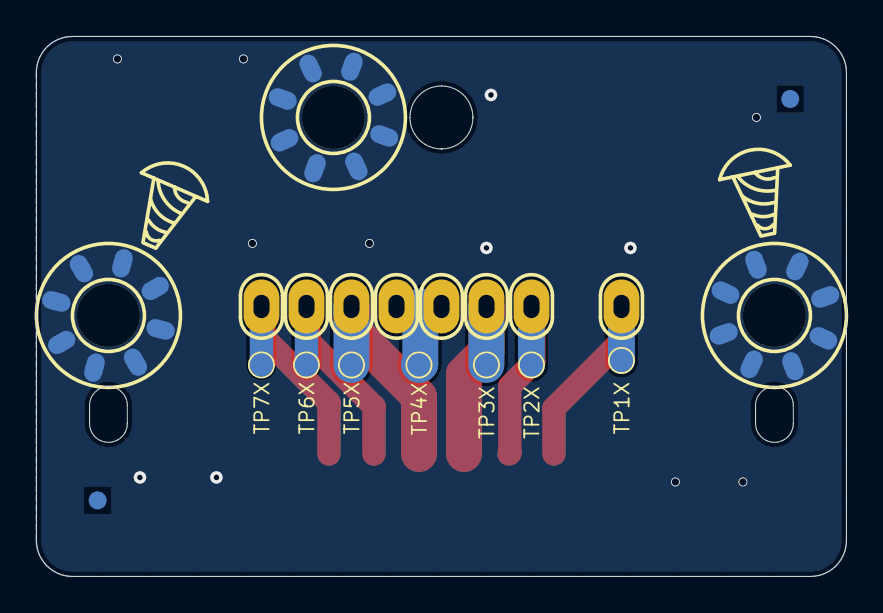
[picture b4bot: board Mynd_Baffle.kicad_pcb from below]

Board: 2 copper layers, 45.0 x 30.0 mm, 18 parts (10 on the bottom side), 8 nets.

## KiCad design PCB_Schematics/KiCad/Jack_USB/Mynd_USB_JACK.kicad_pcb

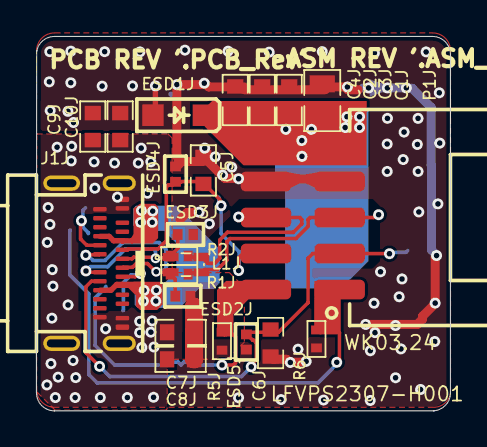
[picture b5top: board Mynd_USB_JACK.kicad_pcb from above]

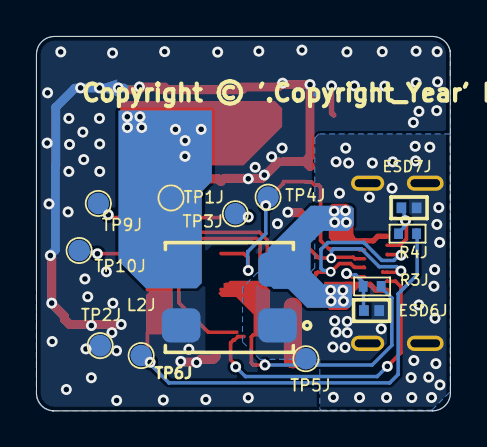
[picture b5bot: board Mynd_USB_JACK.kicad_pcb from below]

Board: 2 copper layers, 23.0 x 20.8 mm, 39 parts (14 on the bottom side), 14 nets.

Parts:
C1J: 2.2uF; C0805_145
C2J, C8J, C10J: 100nF; C0603X100
C3J, C4J: 10nF; C0603X100
C5J, C6J: 470pF; C0603X80
C7J, C9J: 1nF; C0603X100
ESD1J: SMF26AL; SOD-123FL
ESD2J, ESD3J, ESD4J, ESD5J, ESD6J, ESD7J: CESD0501CU; DFN2_100X60X50_65
J1J: NG-HC-0412; USB_TYPE_C_HC_0768
L1J: 90R; CET2012D
L2J: 700R; DU_IND_SMD_SCM7060
P1J: WB200AW-10; WB200AW_2x5P
R1J, R2J, R3J, R4J: 0R; R0402
R5J, R6J: NC; R0402
TP1J, TP2J, TP3J, TP4J, TP5J, TP6J, TP9J, TP10J: TP12; TP120
Teufel_ASM_Label1J: 3.2; Teufel_ASM_Rev
Teufel_Copyright1K: 2023; TEUFEL_COPYRIGHT
Teufel_PCB_Label1J: 3.2; Teufel_PCB_Rev
Teufel_PCB_Logo1K: T.3.0.0040-3.2; Teufel_NoLogo

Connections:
D2_1_N: ESD2J.2, J1J.A7, J1J.B7, L1J.2, R1J.1
D2_1_P: ESD3J.2, J1J.A6, J1J.B6, L1J.1, R2J.1
GND: C1J.2, C2J.2, C3J.2, C4J.2, C5J.2, C6J.2, C7J.2, C8J.2, C9J.2, C10J.2, ESD1J.A, ESD2J.1, ESD3J.1, ESD4J.2, ESD5J.2, L2J.4, P1J.7, P1J.8, R5J.1, R6J.1, TP2J.1
NetC7J_1: C7J.1, C8J.1, C9J.1, C10J.1, ESD6J.1, ESD7J.1, J1J.A1, J1J.A12, J1J.B1, J1J.B12, J1J.G1, J1J.G2, J1J.G3, J1J.G4, L2J.1
NetESD6J_2: ESD6J.2, J1J.A8, R3J.1
NetESD7J_2: ESD7J.2, J1J.B8, R4J.1
NetJ1J_A4: J1J.A4, J1J.A9, J1J.B4, J1J.B9, L2J.2
USB-CC1: C5J.1, ESD4J.1, J1J.A5, P1J.4, TP4J.1
USB-CC2: C6J.1, ESD5J.1, J1J.B5, P1J.3, TP10J.1
USB_J_N: L1J.3, P1J.5, R1J.2, TP9J.1
USB_J_P: L1J.4, P1J.6, R2J.2, TP3J.1
USB_SBU1: P1J.2, R3J.2, R5J.2, TP5J.1
USB_SBU2: P1J.1, R4J.2, R6J.2, TP6J.1
VBUS_C: C1J.1, C2J.1, C3J.1, C4J.1, ESD1J.K, L2J.3, P1J.9, P1J.10, TP1J.1

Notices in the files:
parts and their libraries:
Copyright © '.Copyright_Year' Lautsprecher Teufel GmbH
Teufel Copyright PCB Label
